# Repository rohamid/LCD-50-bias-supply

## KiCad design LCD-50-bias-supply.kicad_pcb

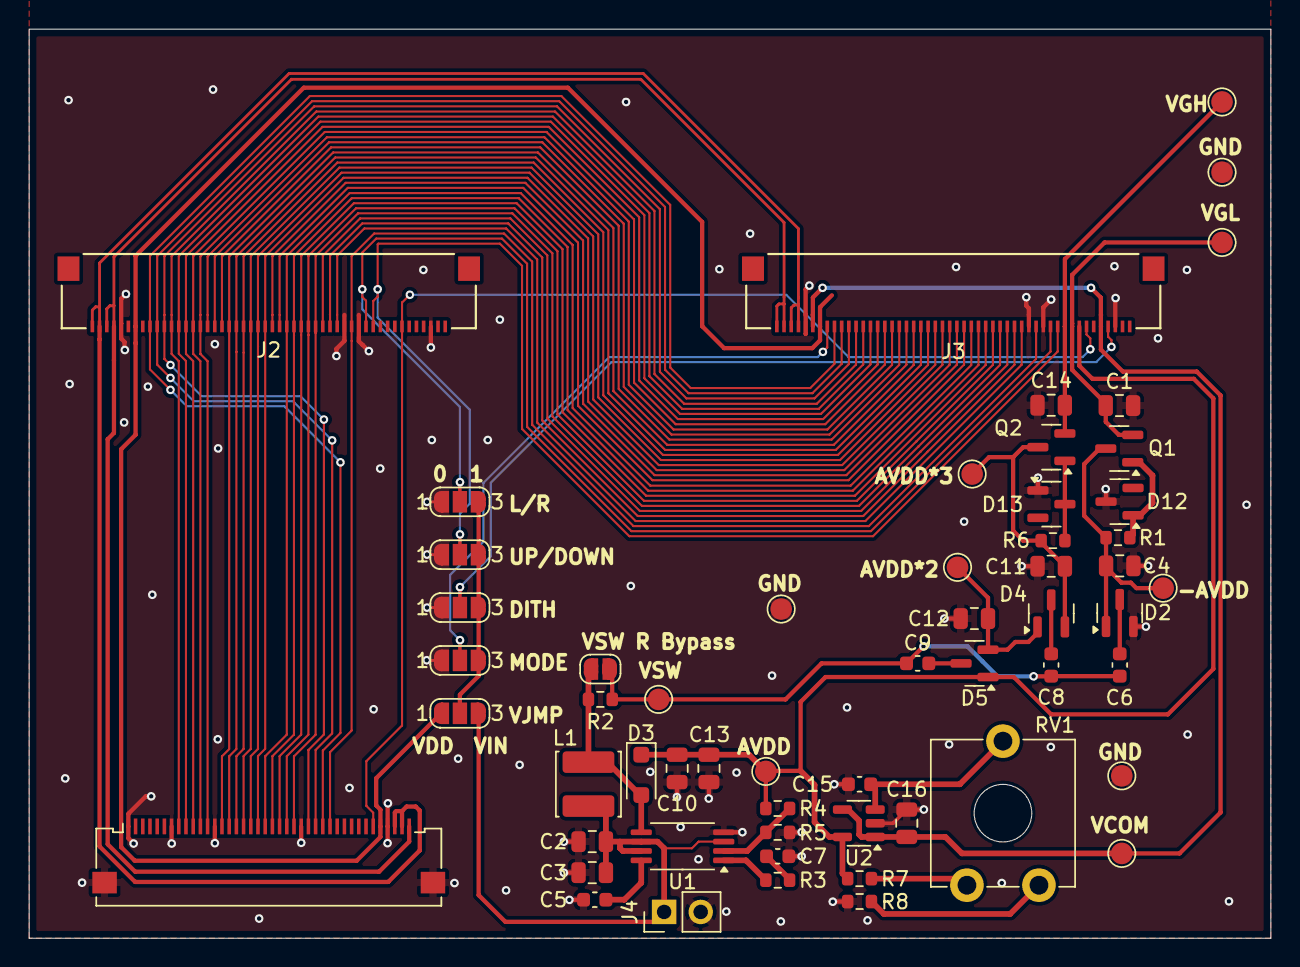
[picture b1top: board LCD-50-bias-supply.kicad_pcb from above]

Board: 2 copper layers, 86.2 x 63.1 mm, 57 parts (0 on the bottom side), 60 nets.

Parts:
C1, C14: 1uF/50V; C_0805_2012Metric
C2, C10, C13: 10uF/25V; C_0805_2012Metric
C3, C16: 1uF/25V; C_0805_2012Metric
C4, C11, C12: 470nF/50V; C_0805_2012Metric
C5, C15: 100nF/25V; C_0603_1608Metric
C6, C8, C9: 100nF/50V; C_0603_1608Metric
C7: 1.1nF/25V; C_0603_1608Metric
D2, D4, D5: BAT54S; SOT-23
D3: MBR0520; D_SOD-123F
D12: BZX84C7V5; SOT-23
D13: BZX84C16; SOT-23
J1: Conn_01x40_MountingPin; Omron_XF2M-4015-1A_1x40-1MP_P0.5mm_Horizontal
J2, J3: Conn_01x50_MountingPin; CON50_1X50_DRB_XF2C_TYC
J4: Conn_01x02; PinHeader_1x02_P2.54mm_Vertical
JP1: JMP; SolderJumper-2_P1.3mm_Open_RoundedPad1.0x1.5mm
JP12, JP13, JP14, JP15, JP16: JMP; SolderJumper-3_P1.3mm_Open_RoundedPad1.0x1.5mm_NumberLabels
L1: 3.3uH; L_Abracon_ASPI-0425
Q1: BC857; SOT-23
Q2: BC850; SOT-23
R1: 1K; R_0603_1608Metric
R2: 10R; R_0603_1608Metric
R3: 30K; R_0603_1608Metric
R4: 120K; R_0603_1608Metric
R5: 18K; R_0603_1608Metric
R6: 1.6K; R_0603_1608Metric
R7, R8: 49.9K; R_0603_1608Metric
RV1: 50K; Potentiometer_ACP_CA9-V10_Vertical_Hole
TP1, TP2, TP3, TP4, TP5, TP6, TP7, TP8, TP9, TP10, TP11: TestPoint; TestPoint_Pad_D1.5mm
U1: TPS61085PW; TSSOP-8_4.4x3mm_P0.65mm
U2: LM7321; SOT-23-5

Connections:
/DCLK: J1.29, J2.14, J3.14
/DE: J1.28, J2.42, J3.42
/DITHB: J3.4, JP15.2 (C)
/HSYNC: J1.26, J2.40, J3.40
/LCD_B0: J2.32, J3.32
/LCD_B1: J2.33, J3.33
/LCD_B2: J2.34, J3.34
/LCD_B3: J1.12, J2.35, J3.35
/LCD_B4: J1.11, J2.36, J3.36
/LCD_B5: J1.10, J2.37, J3.37
/LCD_B6: J1.9, J2.38, J3.38
/LCD_B7: J1.8, J2.39, J3.39
/LCD_G0: J2.24, J3.24
/LCD_G1: J2.25, J3.25
/LCD_G2: J1.19, J2.26, J3.26
/LCD_G3: J1.18, J2.27, J3.27
/LCD_G4: J1.17, J2.28, J3.28
/LCD_G5: J1.16, J2.29, J3.29
/LCD_G6: J1.15, J2.30, J3.30
/LCD_G7: J1.14, J2.31, J3.31
/LCD_R0: J2.16, J3.16
/LCD_R1: J2.17, J3.17
/LCD_R2: J2.18, J3.18
/LCD_R3: J1.24, J2.19, J3.19
/LCD_R4: J1.23, J2.20, J3.20
/LCD_R5: J1.22, J2.21, J3.21
/LCD_R6: J1.21, J2.22, J3.22
/LCD_R7: J1.20, J2.23, J3.23
/L_R_SEL: J2.12, J3.12, JP12.2 (C)
/MODE: J3.43, JP16.2 (C)
/RESET: J1.35, J2.7, J3.7
/U_D_SEL: J2.11, J3.11, JP14.2 (C)
/VSYNC: J1.27, J2.41, J3.41
AVDD: C10.1, C13.1, D3.1 (K), D5.1 (A), J3.8, R4.1, R7.2, TP5.1, U2.5 (V+)
GND: C1.2, C2.2, C3.2, C4.2, C5.1, C7.1, C10.2, C11.2, C12.2, C13.2, C14.2, C15.1, C16.2, D2.2 (K), D12.3 (K), D13.1 (A), J1.1, J1.7, J1.13, J1.25, J1.37, J1.MP (MountPin), J2.3, J2.13, J2.15, J2.46, J3.3, J3.13, J3.15, J3.46, J4.2, JP12.1 (A), JP14.1 (A), JP15.1 (A), JP16.1 (A), R5.2, R8.2, TP8.1, TP9.1, TP10.1, U1.4 (GND), U2.2 (V-)
LED_A: J1.40, J2.47, J2.48, J3.49, J3.50
LED_K: J1.38, J1.39, J2.49, J2.50, J3.47, J3.48
unnamed: C7.2, R3.2
unnamed: C4.1, D2.1 (A), Q1.3 (C), R1.2, TP11.1
unnamed: C6.1, D2.3 (COM)
unnamed: D3.2 (A), JP1.1 (A), L1.2, R2.1, U1.5 (SW)
unnamed: C12.1, D4.1 (A), D5.2 (K), TP3.1
unnamed: C8.2, D4.3 (COM)
unnamed: C11.1, D4.2 (K), Q2.3 (C), R6.2, TP7.1
unnamed: C9.2, D5.3 (COM)
unnamed: D12.1 (A), Q1.1 (B), R1.1
unnamed: D13.3 (K), Q2.1 (B), R6.1
unnamed: C6.2, C8.1, C9.1, JP1.2 (B), R2.2, TP2.1
unnamed: R7.1, RV1.3
unnamed: R8.1, RV1.1
unnamed: R3.1, U1.1 (COMP)
unnamed: R4.2, R5.1, U1.2 (FB)
unnamed: C5.2, U1.8 (SS)
unnamed: C15.2, RV1.2, U2.3 (+)
VCOM: C16.1, J3.5, J3.45, TP6.1, U2.1, U2.4 (-)
VDD: J1.36, J2.44, J3.44, JP13.1 (A)
VDD_JMP: JP12.3 (B), JP13.2 (C), JP14.3 (B), JP15.3 (B), JP16.3 (B)
VGH: C14.1, J3.10, Q2.2 (E), TP4.1
VGL: C1.1, J3.9, Q1.2 (E), TP1.1
VIN: C2.1, C3.1, J4.1, JP13.3 (B), L1.1, U1.3 (EN), U1.6 (VIN), U1.7 (FREQ)

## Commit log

2025-04-20 Change bias supply IC to TPS61085, Finished tracks, TODO: Assigned B.O.M, add more grounding vias
2025-04-23 Changes zener to SOT-23 package, add jobset, generate fabrication file, First release sending to JLCPCB
2025-05-02 Finished, 1st PCB order to JLCPCB
